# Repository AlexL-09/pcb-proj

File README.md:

# pcb-project: Tepig Tamagotchi (w/ evolutions)
Idea:
Use a xiao esp32 c3 and make a tamagotchi with tepig (best pokemon) as the sprite, with plans to add evolution. <br></br>
BOM: <br></br>

<br></br>
Finished PCB:
<br></br>

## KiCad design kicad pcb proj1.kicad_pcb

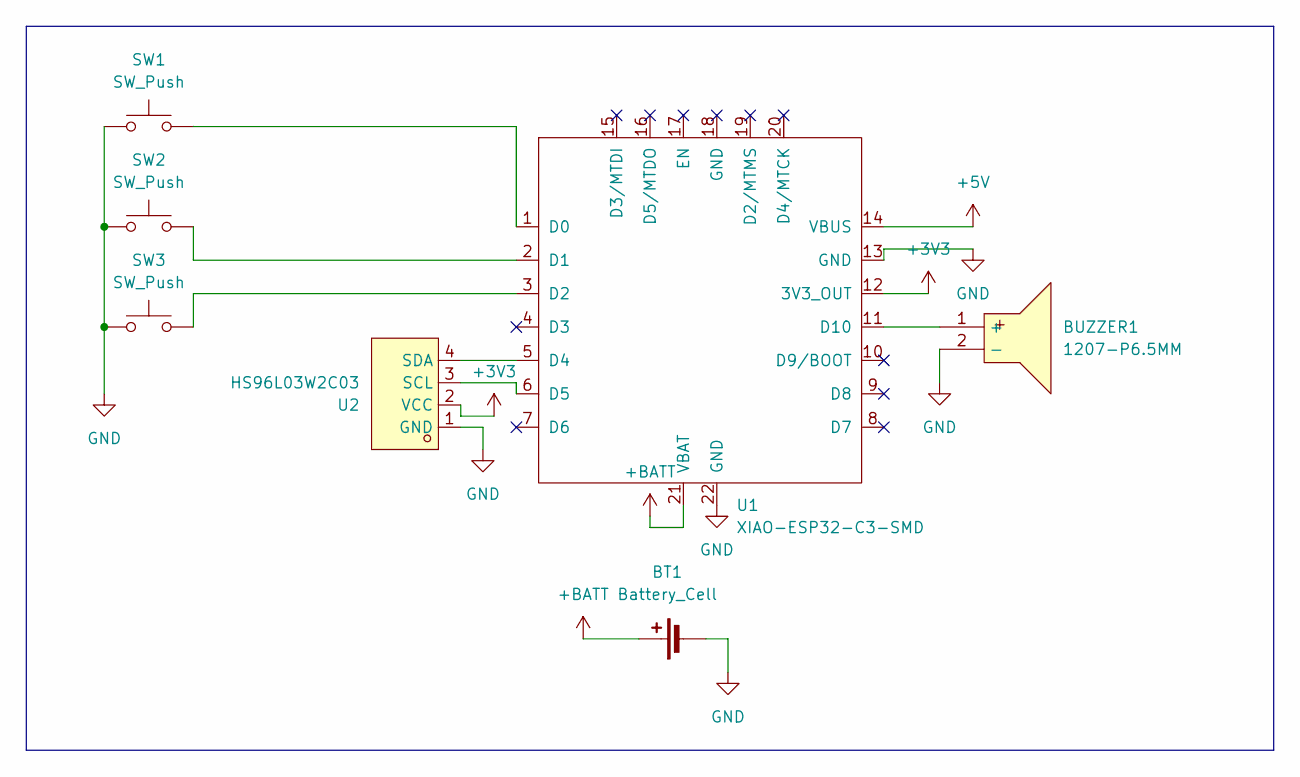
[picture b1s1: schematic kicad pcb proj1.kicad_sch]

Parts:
BT1: Battery_Cell; JST_PH_B2B-PH-SM4-TB_1x02-1MP_P2.00mm_Vertical
BUZZER1: 1207-P6.5MM; BUZ-TH_BD12.5-P6.50-D1.4; MPN 1207-P6.5MM; LCSC Part C49246964
SW1, SW2, SW3: SW_Push; SW-TH_4P-L4.5-W4.5-P3.00-LS4.8
U1: XIAO-ESP32-C3-SMD
U2: HS96L03W2C03; OLED-TH_L27.8-W27.2-P2.54_C9900033791; MPN HS96L03W2C03; LCSC Part C5248080

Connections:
+3V3: U1.12 (3V3_OUT), U2.2 (VCC)
+5V: U1.14 (VBUS)
+BATT: BT1.1 (+), U1.21 (VBAT)
GND: BT1.2 (-), BUZZER1.2 (-), SW1.1, SW2.1, SW3.1, U1.13 (GND), U1.22 (GND), U2.1 (GND)
unnamed: BUZZER1.1 (+), U1.11 (D10)
unnamed: SW1.2, U1.1 (D0)
unnamed: SW2.2, U1.2 (D1)
unnamed: SW3.2, U1.3 (D2)
unnamed: U1.5 (D4), U2.4 (SDA)
unnamed: U1.6 (D5), U2.3 (SCL)

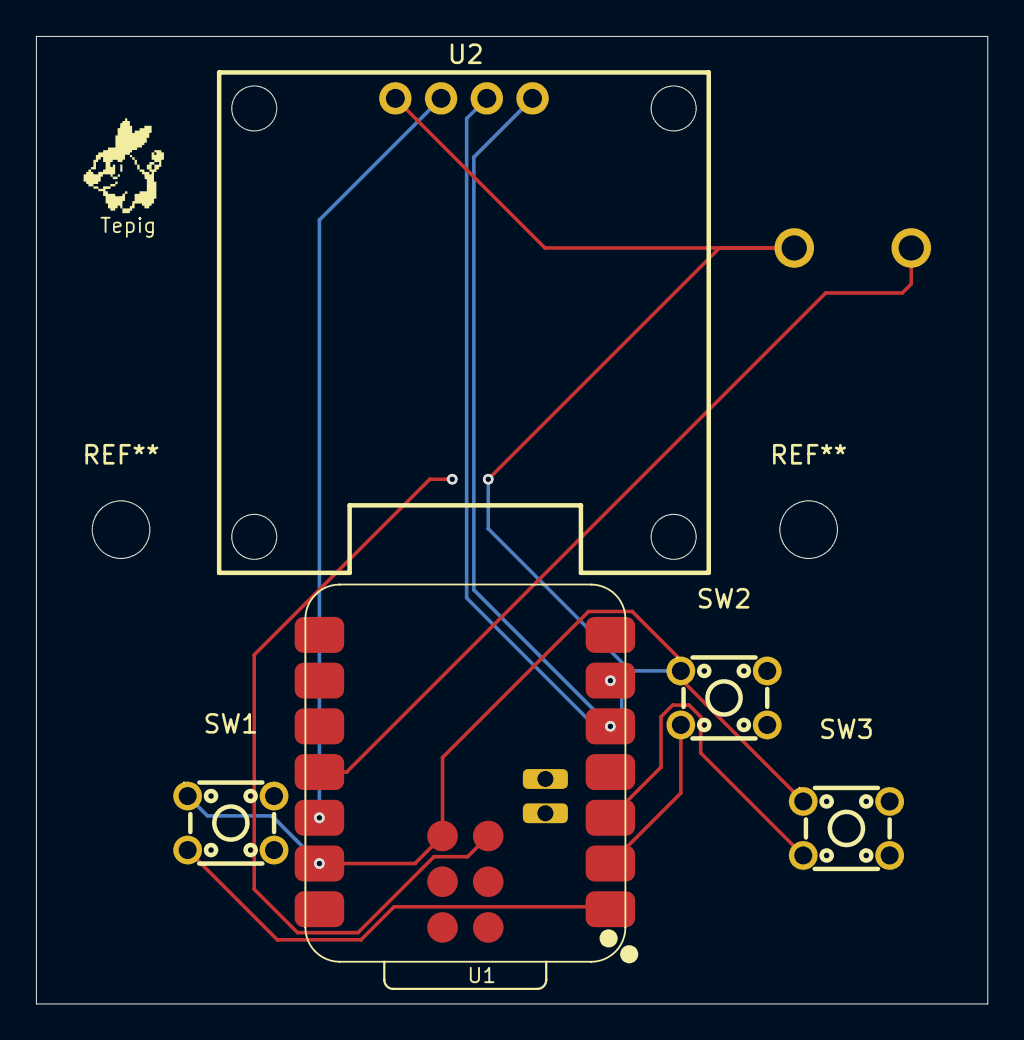
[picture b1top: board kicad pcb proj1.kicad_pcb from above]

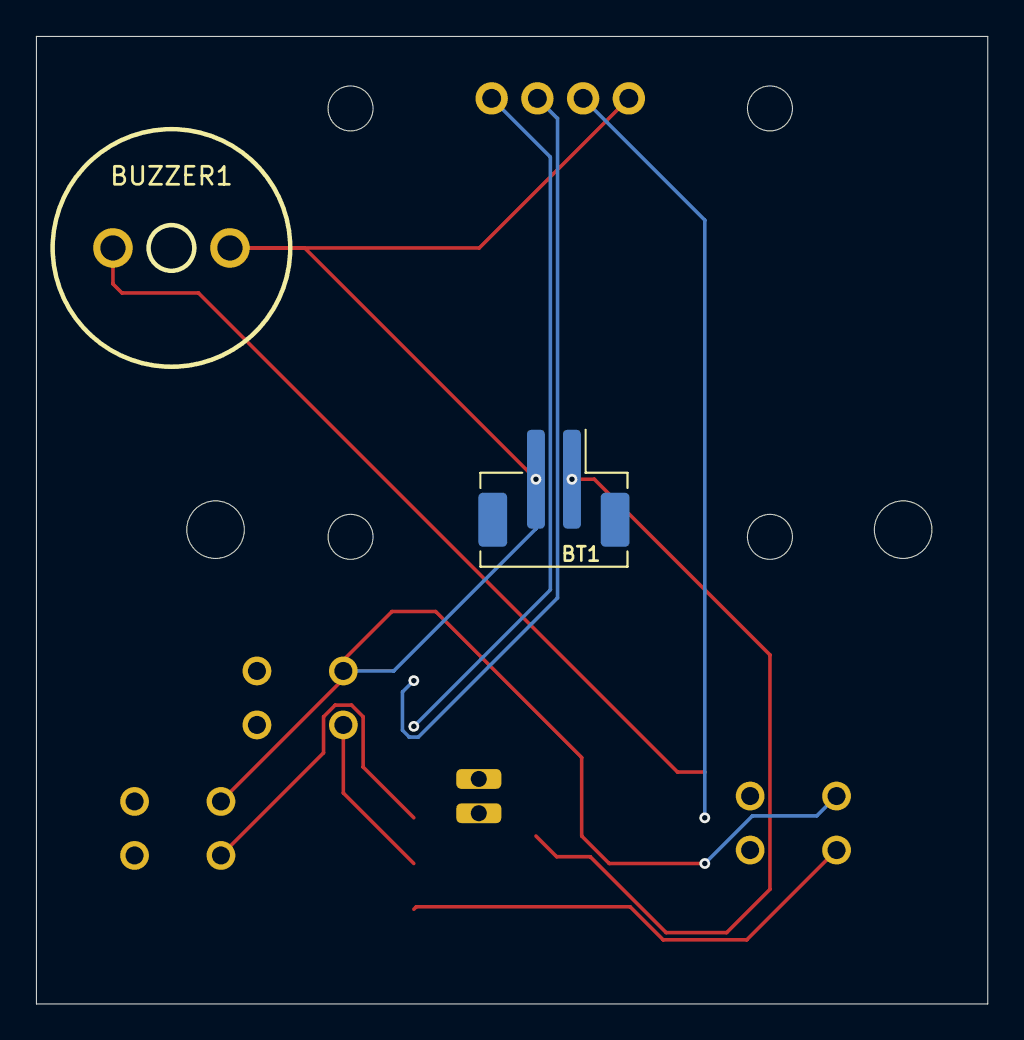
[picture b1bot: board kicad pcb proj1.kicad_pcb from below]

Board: 2 copper layers, 52.8 x 53.8 mm, 8 parts (2 on the bottom side), 9 nets.

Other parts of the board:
Tepig: LOGO; tepigtake2
